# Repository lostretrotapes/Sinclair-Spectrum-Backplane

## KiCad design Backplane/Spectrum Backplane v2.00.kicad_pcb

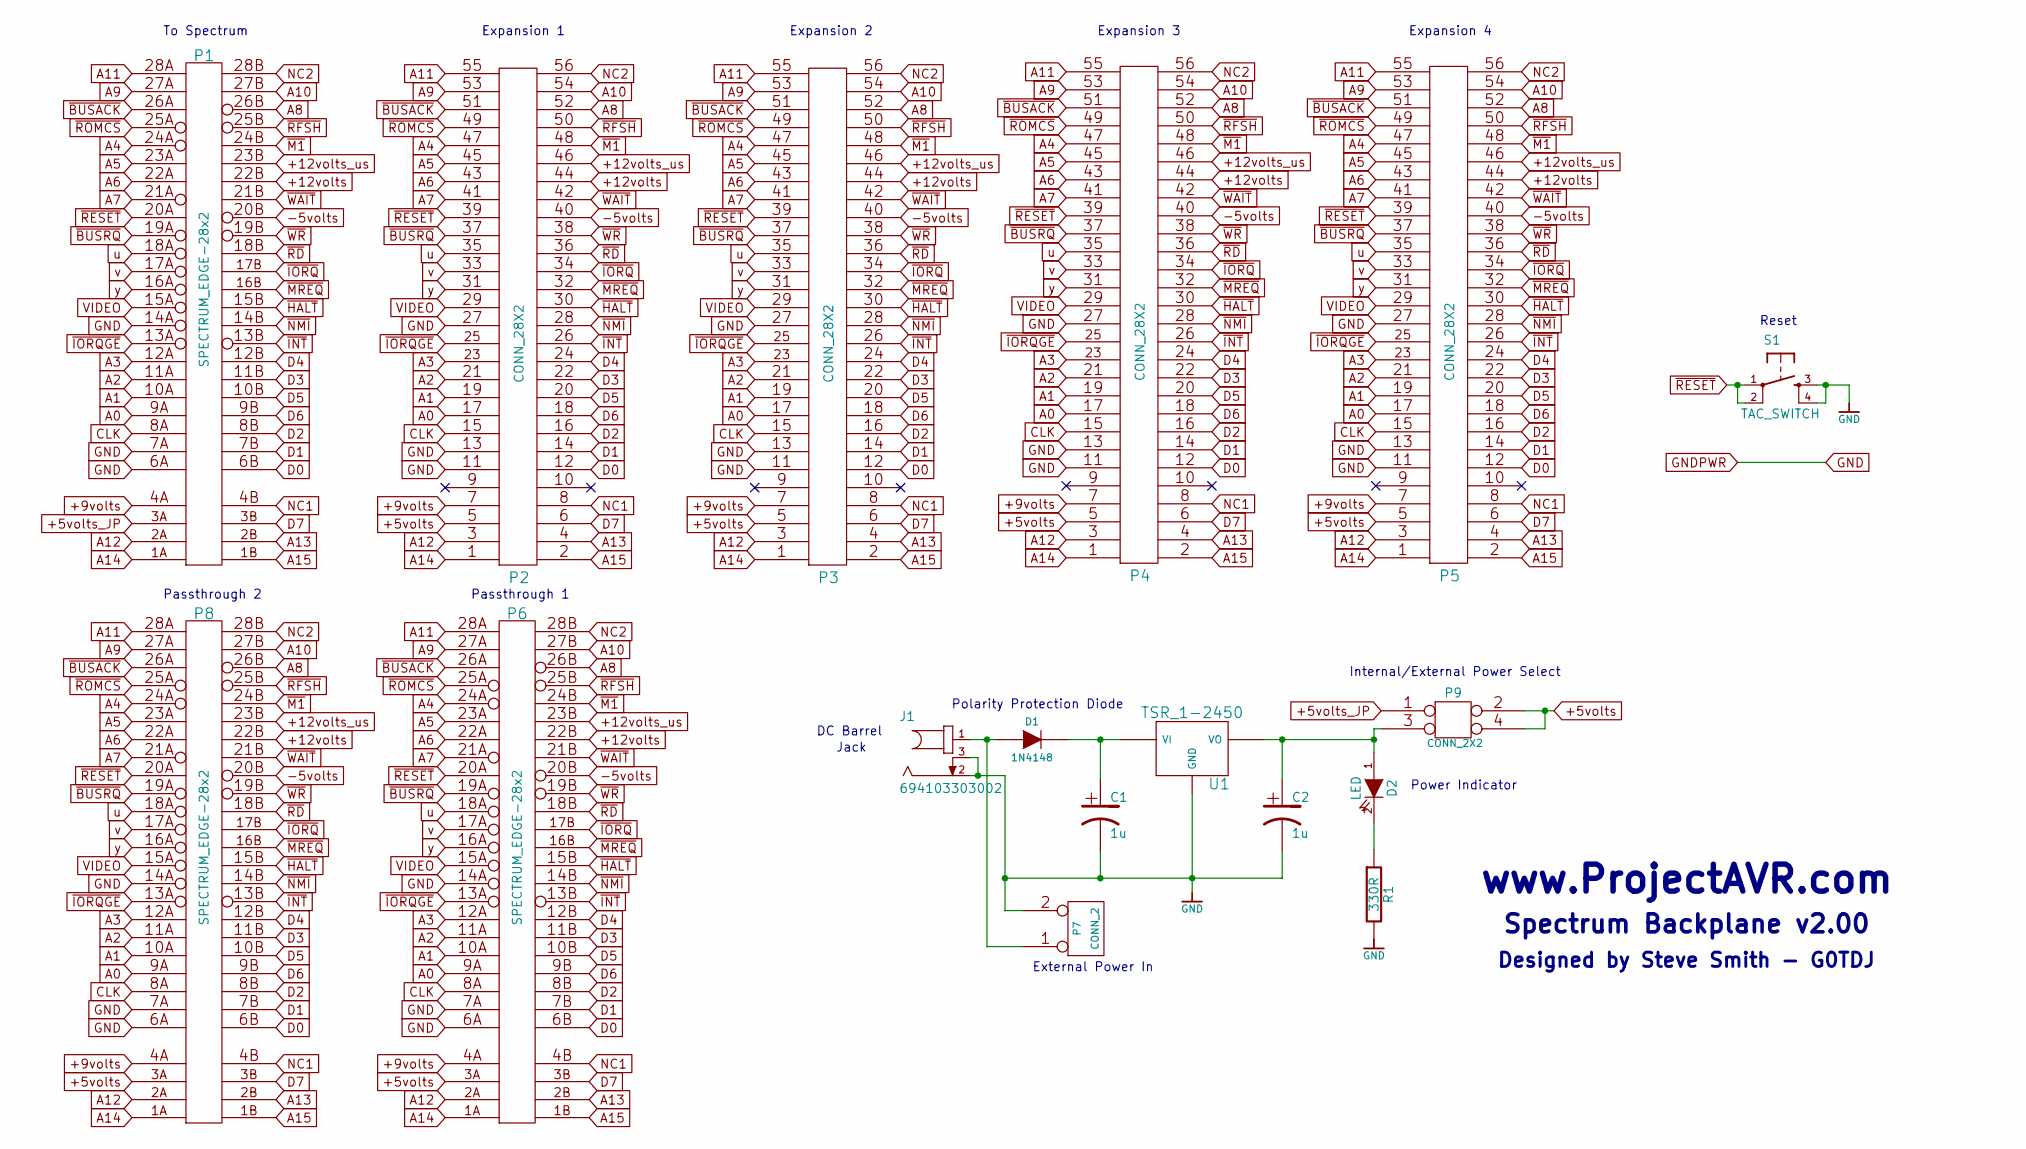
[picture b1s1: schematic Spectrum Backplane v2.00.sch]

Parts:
C1, C2: 1u; CP_Radial_D7.5mm_P2.50mm
D1: 1N4148; 1N4001_Diode_Case_59-10_Axial
D2: LED; LED_D3.0mm
J1: 694103303002; DC_BARREL_JACK
P1, P6, P8: SPECTRUM_EDGE-28x2; ZX_CONN
P2, P3, P4, P5: CONN_28X2; Pin_Header_Straight_2x28_Pitch2.54mm
P7: CONN_2; Pin_Header_Straight_1x02_Pitch2.54mm
P9: CONN_2X2; Pin_Header_Straight_2x02_Pitch2.54mm
R1: 330R; R_Axial_DIN0207_L6.3mm_D2.5mm_P10.16mm_Horizontal
S1: TAC_SWITCH; TACTILE-PTH
U1: TSR_1-2450; TRACO_TSR_1_2450

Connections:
+5volts: P2.5, P3.5, P4.5, P5.5, P6.3A (D7), P8.3A (D7), P9.2, P9.4
+5volts_JP: P1.3A (D7), P9.1
+9volts: P1.4A (N/C), P2.7, P3.7, P4.7, P5.7, P6.4A (N/C), P8.4A (N/C)
+12volts: P1.22B (A6), P2.44, P3.44, P4.44, P5.44, P6.22B (A6), P8.22B (A6)
+12volts_us: P1.23B (A5), P2.46, P3.46, P4.46, P5.46, P6.23B (A5), P8.23B (A5)
-5volts: P1.20B (~RESET), P2.40, P3.40, P4.40, P5.40, P6.20B (~RESET), P8.20B (~RESET)
A0: P1.9A (D6), P2.17, P3.17, P4.17, P5.17, P6.9A (D6), P8.9A (D6)
A1: P1.10A (D5), P2.19, P3.19, P4.19, P5.19, P6.10A (D5), P8.10A (D5)
A2: P1.11A (D3), P2.21, P3.21, P4.21, P5.21, P6.11A (D3), P8.11A (D3)
A3: P1.12A (D4), P2.23, P3.23, P4.23, P5.23, P6.12A (D4), P8.12A (D4)
A4: P1.24A (~M1), P2.47, P3.47, P4.47, P5.47, P6.24A (~M1), P8.24A (~M1)
A5: P1.23A (+12volts_unsmoothed), P2.45, P3.45, P4.45, P5.45, P6.23A (+12volts_unsmoothed), P8.23A (+12volts_unsmoothed)
A6: P1.22A (+12volts), P2.43, P3.43, P4.43, P5.43, P6.22A (+12volts), P8.22A (+12volts)
A7: P1.21A (~WAIT), P2.41, P3.41, P4.41, P5.41, P6.21A (~WAIT), P8.21A (~WAIT)
A8: P1.26B (~BUSACK), P2.52, P3.52, P4.52, P5.52, P6.26B (~BUSACK), P8.26B (~BUSACK)
A9: P1.27A (A10), P2.53, P3.53, P4.53, P5.53, P6.27A (A10), P8.27A (A10)
A10: P1.27B (A9), P2.54, P3.54, P4.54, P5.54, P6.27B (A9), P8.27B (A9)
A11: P1.28A (N/C), P2.55, P3.55, P4.55, P5.55, P6.28A (N/C), P8.28A (N/C)
A12: P1.2A (A13), P2.3, P3.3, P4.3, P5.3, P6.2A (A13), P8.2A (A13)
A13: P1.2B (A12), P2.4, P3.4, P4.4, P5.4, P6.2B (A12), P8.2B (A12)
A14: P1.1A (A15), P2.1, P3.1, P4.1, P5.1, P6.1A (A15), P8.1A (A15)
A15: P1.1B (A14), P2.2, P3.2, P4.2, P5.2, P6.1B (A14), P8.1B (A14)
CLK: P1.8A (D2), P2.15, P3.15, P4.15, P5.15, P6.8A (D2), P8.8A (D2)
D0: P1.6B (GND), P2.12, P3.12, P4.12, P5.12, P6.6B (GND), P8.6B (GND)
D1: P1.7B (GND), P2.14, P3.14, P4.14, P5.14, P6.7B (GND), P8.7B (GND)
D2: P1.8B (CLK), P2.16, P3.16, P4.16, P5.16, P6.8B (CLK), P8.8B (CLK)
D3: P1.11B (A2), P2.22 (eP22), P3.22 (eP22), P4.22 (eP22), P5.22 (eP22), P6.11B (A2), P8.11B (A2)
D4: P1.12B (A3), P2.24, P3.24, P4.24, P5.24, P6.12B (A3), P8.12B (A3)
D5: P1.10B (A1), P2.20, P3.20, P4.20, P5.20, P6.10B (A1), P8.10B (A1)
D6: P1.9B (A0), P2.18, P3.18, P4.18, P5.18, P6.9B (A0), P8.9B (A0)
D7: P1.3B (+5volts), P2.6, P3.6, P4.6, P5.6, P6.3B (+5volts), P8.3B (+5volts)
GND: C1.2, C2.2, J1.2, J1.3, P1.6A (D0), P1.7A (D1), P1.14A (~NMI), P2.11, P2.13, P2.27, P3.11, P3.13, P3.27, P4.11, P4.13, P4.27, P5.11, P5.13, P5.27, P6.6A (D0), P6.7A (D1), P6.14A (~NMI), P7.2 (PM), P8.6A (D0), P8.7A (D1), P8.14A (~NMI), R1.2, S1.3, S1.4, U1.2 (GND)
NC1: P1.4B (+9volts), P2.8, P3.8, P4.8, P5.8, P6.4B (+9volts), P8.4B (+9volts)
NC2: P1.28B (A11), P2.56, P3.56, P4.56, P5.56, P6.28B (A11), P8.28B (A11)
unnamed: C1.1, D1.2 (K), U1.1 (VI)
unnamed: C2.1, D2.1 (A), P9.3, U1.3 (VO)
unnamed: D1.1 (A), J1.1, P7.1
unnamed: D2.2 (K), R1.1
VIDEO: P1.15A (~HALT), P2.29, P3.29, P4.29, P5.29, P6.15A (~HALT), P8.15A (~HALT)
u: P1.18A (~RD), P2.35, P3.35, P4.35, P5.35, P6.18A (~RD), P8.18A (~RD)
v: P1.17A (~IORQ), P2.33, P3.33, P4.33, P5.33, P6.17A (~IORQ), P8.17A (~IORQ)
y: P1.16A (~MREQ), P2.31, P3.31, P4.31, P5.31, P6.16A (~MREQ), P8.16A (~MREQ)
~BUSACK: P1.26A (A8), P2.51, P3.51, P4.51, P5.51, P6.26A (A8), P8.26A (A8)
~BUSRQ: P1.19A (~WR), P2.37, P3.37, P4.37, P5.37, P6.19A (~WR), P8.19A (~WR)
~HALT: P1.15B (VIDEO), P2.30, P3.30, P4.30, P5.30, P6.15B (VIDEO), P8.15B (VIDEO)
~INT: P1.13B (~IORQGE), P2.26, P3.26, P4.26, P5.26, P6.13B (~IORQGE), P8.13B (~IORQGE)
~IORQ: P1.17B (v), P2.34, P3.34, P4.34, P5.34, P6.17B (v), P8.17B (v)
~IORQGE: P1.13A (!INT), P2.25, P3.25, P4.25, P5.25, P6.13A (!INT), P8.13A (!INT)
~M1: P1.24B (A4), P2.48, P3.48, P4.48, P5.48, P6.24B (A4), P8.24B (A4)
~MREQ: P1.16B (y), P2.32, P3.32, P4.32, P5.32, P6.16B (y), P8.16B (y)
~NMI: P1.14B (GND), P2.28, P3.28, P4.28, P5.28, P6.14B (GND), P8.14B (GND)
~RD: P1.18B (u), P2.36, P3.36, P4.36, P5.36, P6.18B (u), P8.18B (u)
~RESET: P1.20A (-5volts), P2.39, P3.39, P4.39, P5.39, P6.20A (-5volts), P8.20A (-5volts), S1.1, S1.2
~RFSH: P1.25B (~ROMCS), P2.50, P3.50, P4.50, P5.50, P6.25B (~ROMCS), P8.25B (~ROMCS)
~ROMCS: P1.25A (~RFSH), P2.49, P3.49, P4.49, P5.49, P6.25A (~RFSH), P8.25A (~RFSH)
~WAIT: P1.21B (A7), P2.42, P3.42, P4.42, P5.42, P6.21B (A7), P8.21B (A7)
~WR: P1.19B (~BUSRQ), P2.38, P3.38, P4.38, P5.38, P6.19B (~BUSRQ), P8.19B (~BUSRQ)

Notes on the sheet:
To Spectrum
Passthrough 2
Passthrough 1
Expansion 1
Expansion 2
Expansion 3
Expansion 4
Internal/External Power Select
Power Indicator
Polarity Protection Diode
DC Barrel
Jack
External Power In
Reset
Spectrum Backplane v2.00
Designed by Steve Smith - G0TDJ
www.ProjectAVR.com

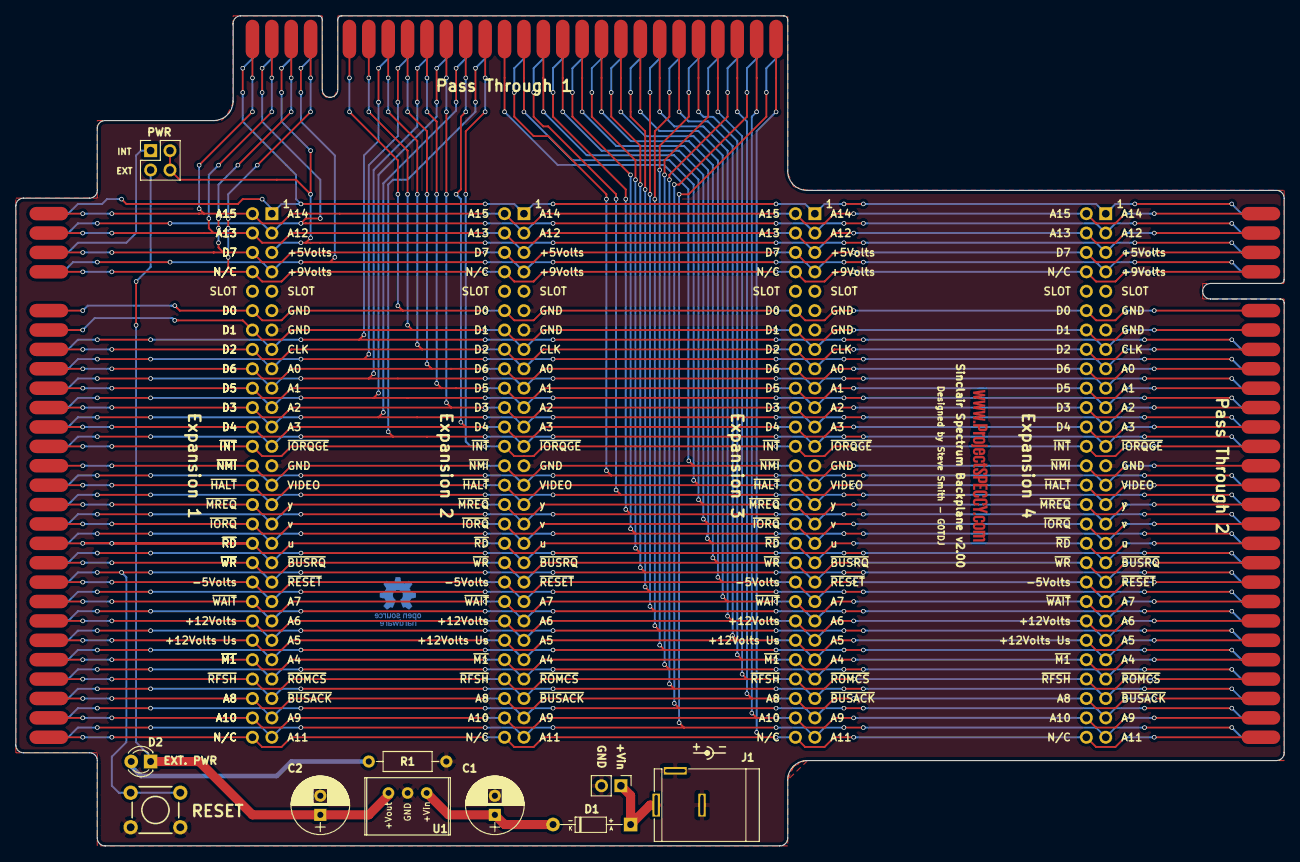
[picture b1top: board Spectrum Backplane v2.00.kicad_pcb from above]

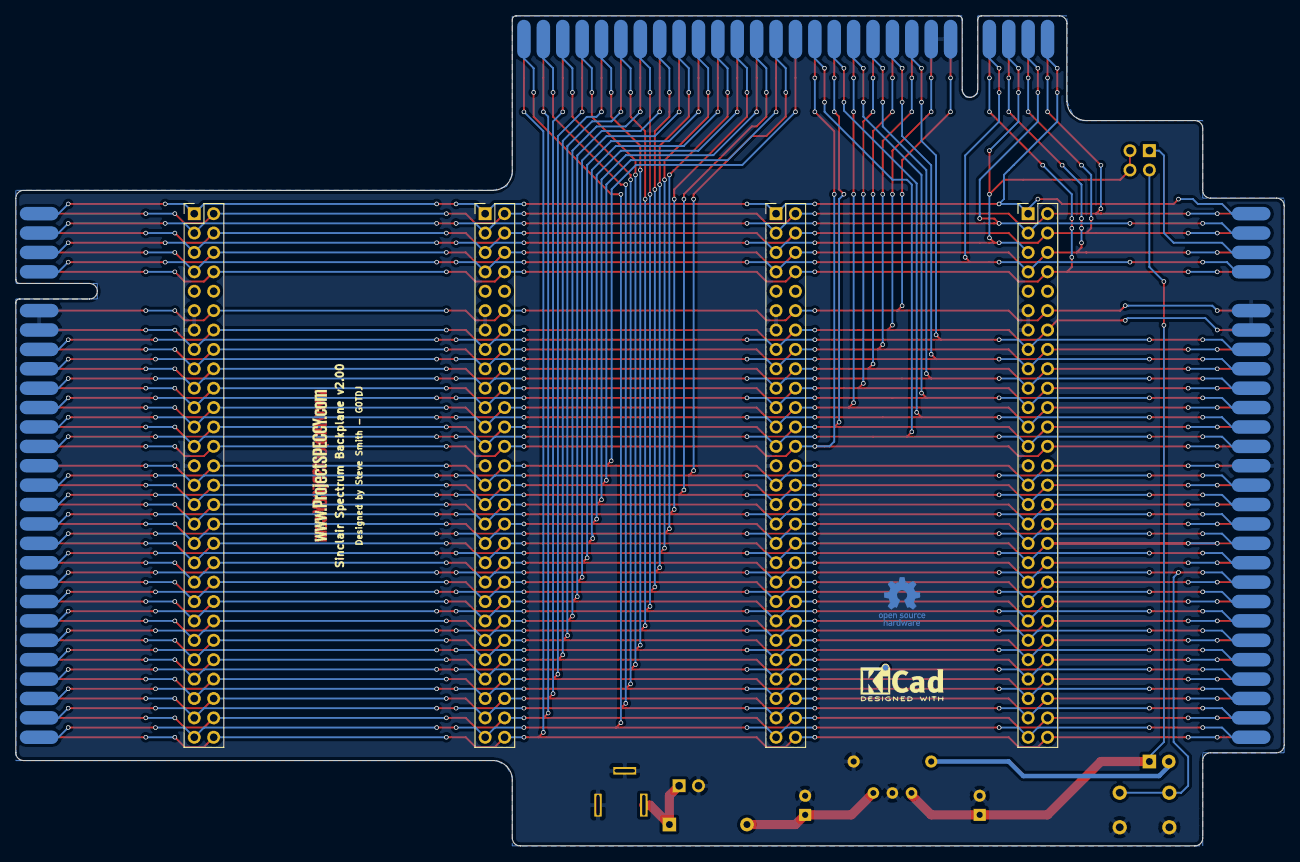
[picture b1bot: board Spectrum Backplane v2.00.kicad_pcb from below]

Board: 2 copper layers, 166.1 x 108.7 mm, 17 parts (4 on the bottom side), 57 nets.
